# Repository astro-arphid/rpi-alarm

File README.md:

With gravitational waves expected to be arriving thick and fast in the upcoming O3 run of Advanced LIGO, we need to be alert! GW Astronomers and their professional EM counterparts have access to real-time data on the status of the instruments and the latest candidate events, but we would like to share the news with students and staff in the dept by creating a gravitational-wave alarm. This project aims to develop a low-cost device which interface with LIGO's realtime systems and display detector and trigger information on simple hardware. It will involve a blend of programming and electronics based on a raspberry pi to process data and control displays. Advanced functionality may include a voice or touch-screen interface. Once prototyped, the design can be documented and used in outreach programmes at Glasgow and other LSC institutions.

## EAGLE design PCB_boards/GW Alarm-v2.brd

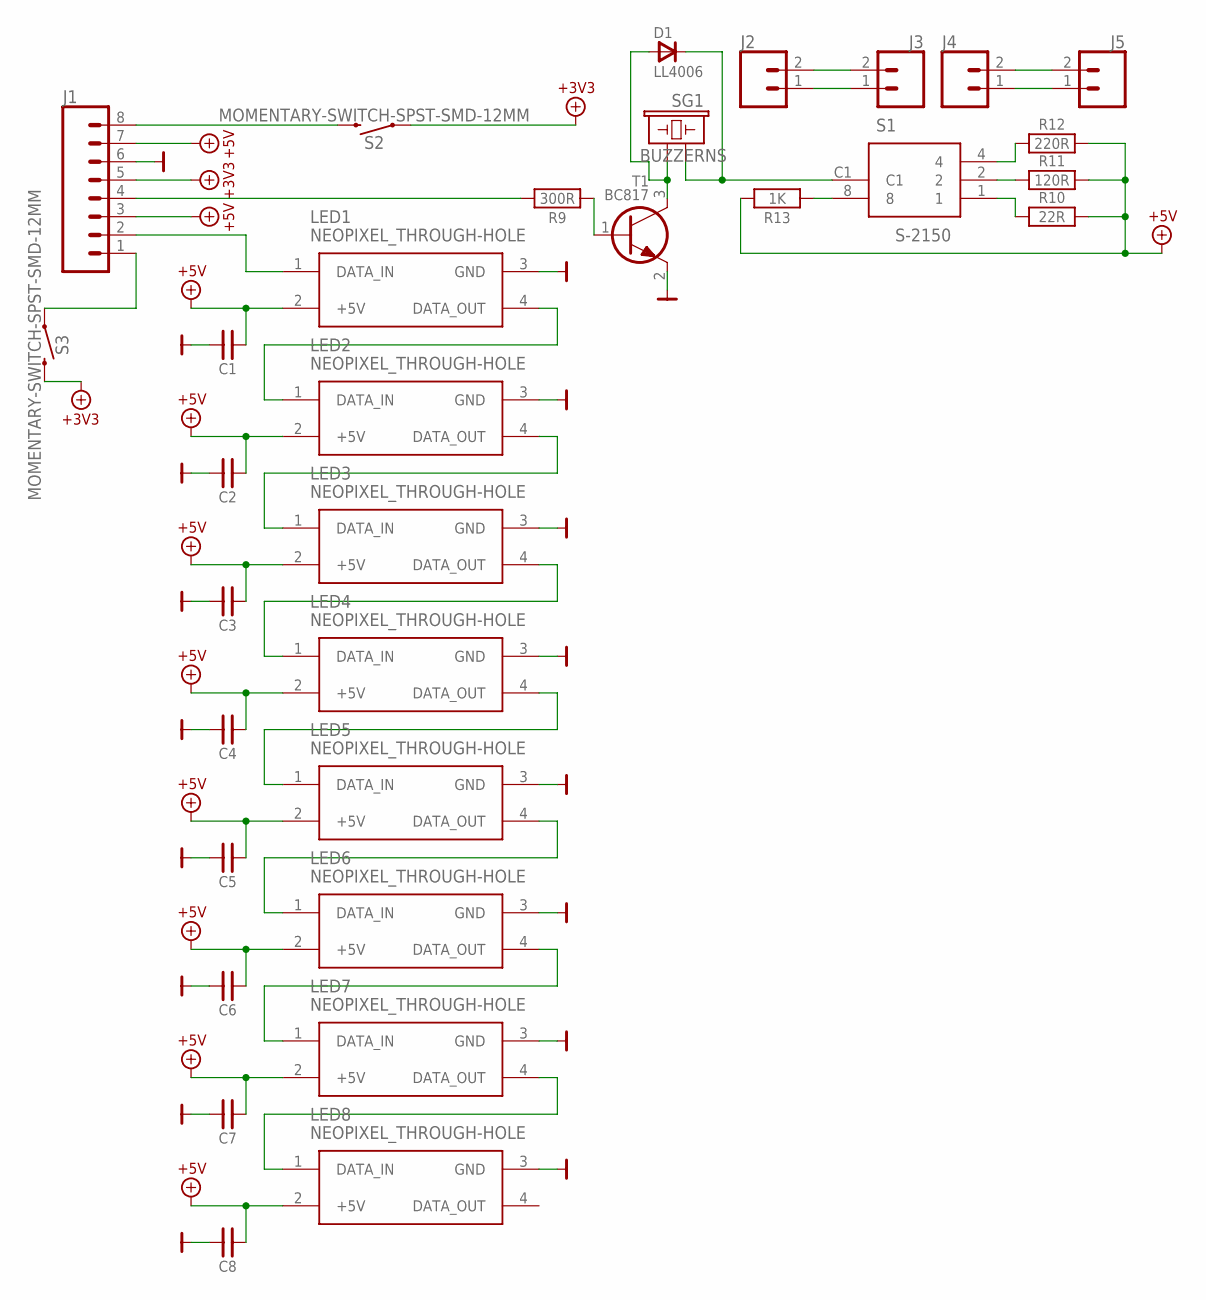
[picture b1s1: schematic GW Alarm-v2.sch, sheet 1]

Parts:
C1, C2, C3, C4, C5, C6, C7, C8: C1206
D1: LL4006; DMELF-VALUE
J1: CONN_083.5MM-8; SCREWTERMINAL-3.5MM-8
J2, J4: CONN_023.5MM; SCREWTERMINAL-3.5MM-2
J3, J5: CONN_02LOCK_LONGPADS; 1X02_LOCK_LONGPADS
LED1, LED2, LED3, LED4, LED5, LED6, LED7, LED8: NEOPIXEL_THROUGH-HOLE
R9: 300R; R1206
R10: 22R; R1206
R11: 120R; R1206
R12: 220R; R1206
R13: 1K; R1206
S1: S-2150; S2150
S2, S3: MOMENTARY-SWITCH-SPST-SMD-12MM; TACTILE_SWITCH_SMD_12MM
SG1: BUZZERNS; BUZZER-12MM-NS
T1: BC817; SOT23

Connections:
+3V3: J1.5, S2.1, S3.3 (2)
+5V: C1.1, C2.1, C3.1, C4.1, C5.1, C6.1, C7.1, C8.1, J1.3, J1.7, LED1.2 (+5V), LED2.2 (+5V), LED3.2 (+5V), LED4.2 (+5V), LED5.2 (+5V), LED6.2 (+5V), LED7.2 (+5V), LED8.2 (+5V), R10.2, R11.2, R12.2, R13.2
GND: C1.2, C2.2, C3.2, C4.2, C5.2, C6.2, C7.2, C8.2, J1.6, LED1.3 (GND), LED2.3 (GND), LED3.3 (GND), LED4.3 (GND), LED5.3 (GND), LED6.3 (GND), LED7.3 (GND), LED8.3 (GND), T1.2 (E)
unnamed: D1.A, SG1.- (2), T1.3 (C)
unnamed: R9.1, T1.1 (B)
unnamed: R10.1, S1.1
unnamed: R11.1, S1.2
unnamed: R12.1, S1.4
unnamed: R13.1, S1.8
unnamed: LED1.4 (DATA_OUT), LED2.1 (DATA_IN)
unnamed: LED2.4 (DATA_OUT), LED3.1 (DATA_IN)
unnamed: LED3.4 (DATA_OUT), LED4.1 (DATA_IN)
unnamed: LED4.4 (DATA_OUT), LED5.1 (DATA_IN)
unnamed: LED5.4 (DATA_OUT), LED6.1 (DATA_IN)
unnamed: LED6.4 (DATA_OUT), LED7.1 (DATA_IN)
unnamed: LED7.4 (DATA_OUT), LED8.1 (DATA_IN)
unnamed: J1.2, LED1.1 (DATA_IN)
unnamed: J1.4, R9.2
unnamed: D1.C, S1.C1, SG1.+ (1)
unnamed: J1.1, S3.1
unnamed: J1.8, S2.3 (2)
unnamed: J2.1, J3.1
unnamed: J2.2, J3.2
unnamed: J4.1, J5.1
unnamed: J4.2, J5.2

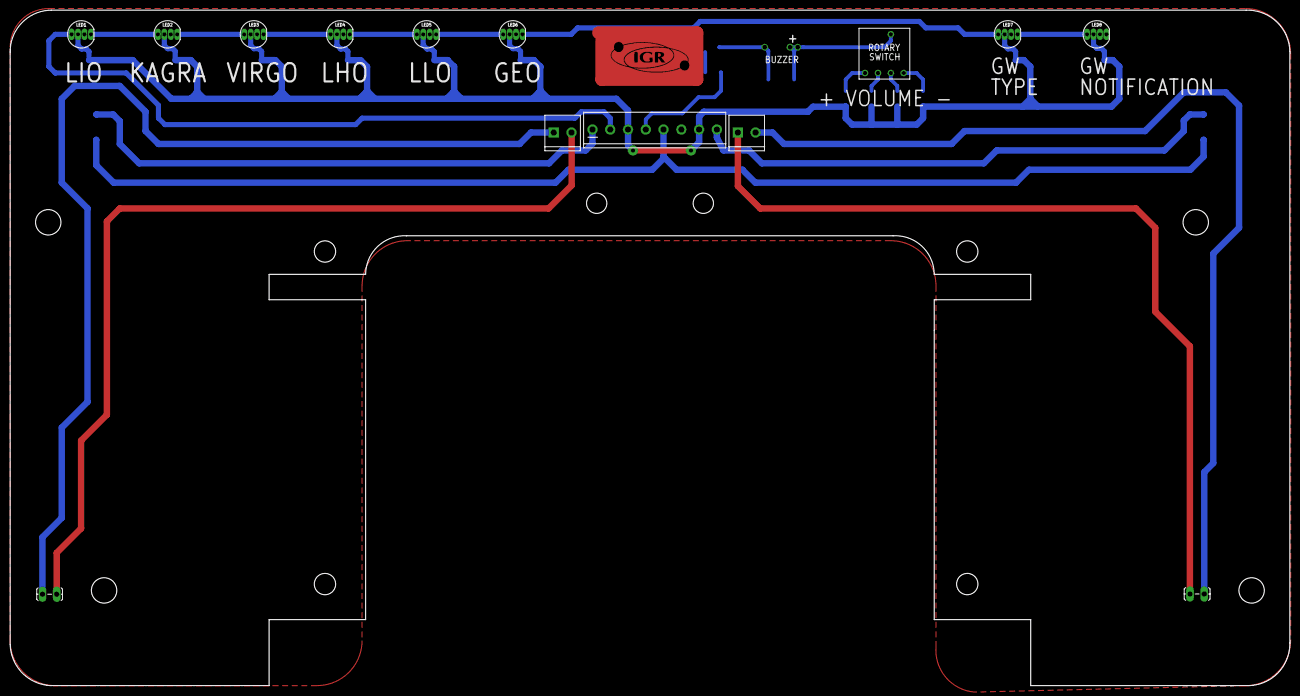
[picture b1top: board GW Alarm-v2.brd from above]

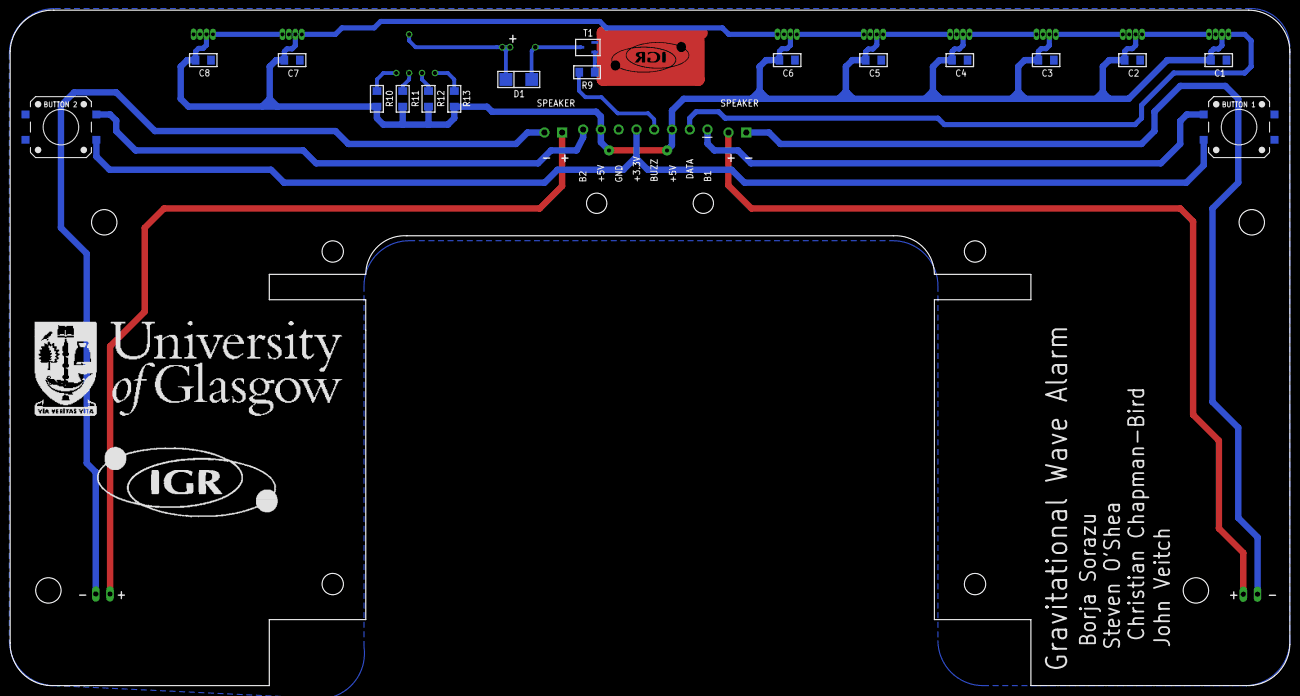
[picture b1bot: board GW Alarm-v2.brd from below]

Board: 2 copper layers, 252.0 x 133.0 mm, 35 parts (19 on the bottom side), 25 nets.

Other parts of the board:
U$1, U$4: IGRLOGO#PNG
U$3: GLASGOWUNIVERSITY#GIF

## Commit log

2024-01-16 Spaces converted to tabs
2024-01-16 Tidying up
2024-01-16 Added requirements file with known working python packages on Debian 12

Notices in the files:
parts and their libraries:
SparkFun: Licensing: CC v3.0 Share-Alike You are welcome to use this library for commercial purposes.
SparkFun-Connectors: Licensing: Creative Commons ShareAlike 4.0 International - https://creativecommons.org/licenses/by-sa/4.0
